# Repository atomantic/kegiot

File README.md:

Kegiot
=======
DIY Internet of Things (IoT) smart beverage dispenser.

This was a weekend hack project that turned into a maintained beverage dispenser.

I'll be giving a talk on this and touring the codebase as well as how the device was put together at [LinuxFest Northwest 2016](https://www.linuxfestnorthwest.org/2016)

Talk in progress: http://adameivy.com/presentation_kegerator/

# Warning
This codebase has been ported from a particular setup. Authentication was removed (as it was a proprietary setup).
The creator of this codebase assumes no responsibility for stolen beverages.

# Developer Getting Started
Assumes you are on OSX (yeah, we are opinionated).
You don't need to have a Beagle Bone Black connected to just run the app and test it. The app will mock all hardware interfaces.

```
# fork it
# clone it
cd kegiot
./dev init
```

This will make sure you have node.js and global module installations for `gulp`, `bower`, `npm-check` and will run `npm install && bower install`. Once ready, it will run `gulp`, which will launch the Admin UI. The UI will be running in `desktop` mode, which will mock all of the hardware interfaces (LCD, RFID scanner, temperature monitoring, ballvalve controller, etc).

## Authentication
This app has stripped out the authentication mechanism (because it was a proprietary auth service). You'll need to wire in your own to identify admin users or restrict access to the UI another way.
If you add auth:
* remove `.isAdmin.isAuthed` from `app/server/views/index.jade`
* re-enable the `requireAdmin` logic in `app/server/lib/common.js`
* remove default object keys from `app/client/js/app.js` in App.user (should be empty object)
* enable any place in the code where you find `authLib` (replace with auth solution)

## Slack notifications
You will need to supply your own slack hook URL as an env `SLACKHOOK` if you want the watchdog to notify temperature and keg volume limits as well as broadcast the location of the admin UI.

## Beagle Bone Black

0. Make sure you have setup a non-root user
```
apt-get update
useradd bbb
password bbb
password root
echo "bbb ALL=(ALL) ALL" >> /etc/sudoers
mkhomedir_helper bbb
mkdir -p /opt/kegiot
chown -R bbb:bbb /opt/kegiot
su bbb
chsh /bin/bash
curl -o- https://raw.githubusercontent.com/creationix/nvm/v0.31.1/install.sh | bash
. ~/.bashrc
nvm install 4.4.5
```
1. Plugin an ethernet cable and USB
2. Run the BBB install script
```
./dev install
```
3. Deploy the code
```
./dev deploy
```

## Deploy to the Bone branch
in order to allow the Beagleboard to not have to install gulp, sass, etc and build the project on the board, we publish the built output of the UI (post-sass) via:
```
gulp deploy
```
After that, we can `git pull` on the Beagleboard and we've got the built UI.
This assumes you went through and installed git, created an ssh key on the board (if needed) and deployed the whole codebase via git.
Alternatively, you can use the `dev` script to continue to deploy partial code without rebuilds or git.

## Guides
http://elinux.org/Beagleboard:BeagleBoneBlack_Debian

http://beagleboard.org/support/bonescript

## i2c (LCD)

Check the pinout here: http://beagleboard.org/static/images/cape-headers.png

Connect the Ground, 5v, 3v, clock, data to the bbb.
skip VDD_5V as it is only available when the Bone is plugged into the 5V power outlet. You can use the SYS_5V when only plugged into USB on your computer.

http://www.bibase.com/ascii.htm

```
ssh root@192.168.7.2
root@beaglebone:/var/lib/cloud9/myScripts# i2cset 1 0x04 0x63 0x40 0x00 0x00 i
root@beaglebone:/var/lib/cloud9/myScripts# i2cset 1 0x04 0x68 0x40 0x00 0x00 i
root@beaglebone:/var/lib/cloud9/myScripts# i2cset 1 0x04 0x70 0x00 0x00 0x00 0x48 0x69 0x64 0x65 0x79 0x20 0x68 0x6F i
```

The above are the commands that clear the lcd, home the cursor and print the message "Hidey ho"

# License
ISC

# Contributing
We welcome pull-requests. Feel free to fork, and deviate! Drink on.

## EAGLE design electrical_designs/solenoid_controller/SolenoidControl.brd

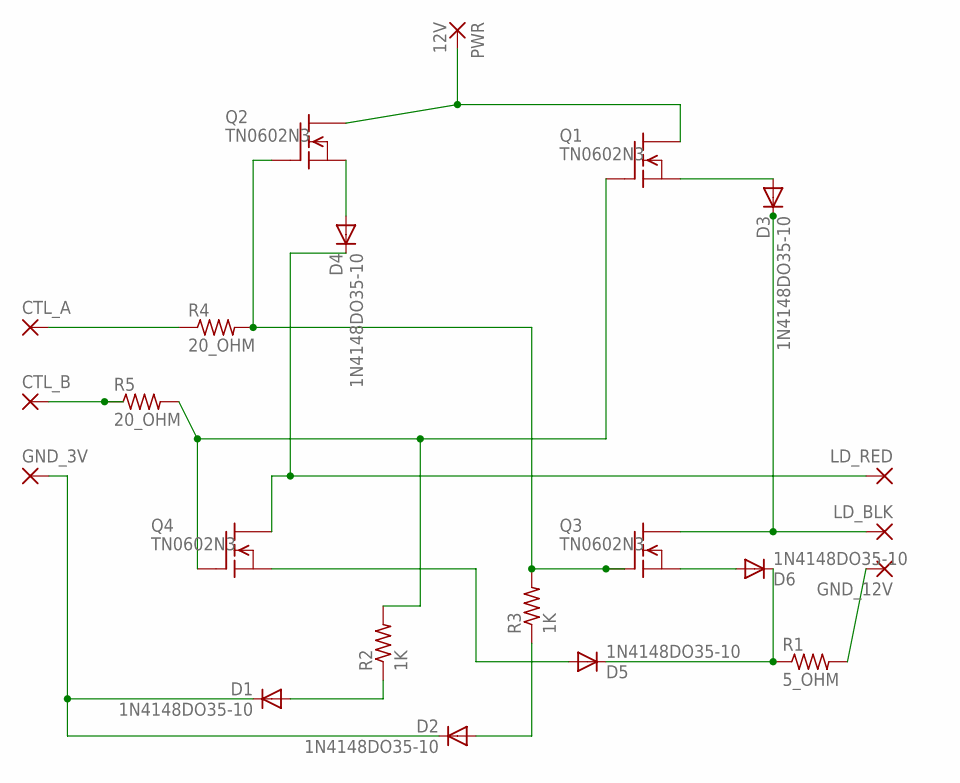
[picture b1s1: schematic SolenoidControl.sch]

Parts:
CTL_A: 2,15/1,0
CTL_B: 2,15/1,0
D1, D2, D3, D4, D5, D6: 1N4148DO35-10; DO35-10
GND_3V, GND_12V: 2,15/1,0
LD_BLK: 2,15/1,0
LD_RED: 2,15/1,0
PWR: 12V; 2,15/1,0
Q1, Q2, Q3, Q4: TN0602N3; TO-92
R1: 5_OHM; 0207/12
R2, R3: 1K; 0207/12
R4, R5: 20_OHM; 0207/12

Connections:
unnamed: PWR.1, Q1.3 (D), Q2.3 (D)
unnamed: D3.A, Q1.1 (S)
unnamed: D4.A, Q2.1 (S)
unnamed: D4.C, LD_RED.1, Q4.3 (D)
unnamed: D3.C, LD_BLK.1, Q3.3 (D)
unnamed: GND_12V.1, R1.2
unnamed: D5.A, Q4.1 (S)
unnamed: D2.A, R3.1
unnamed: Q2.2 (G), Q3.2 (G), R3.2, R4.2
unnamed: Q1.2 (G), Q4.2 (G), R2.2, R5.2
unnamed: CTL_B.1, R5.1
unnamed: CTL_A.1, R4.1
unnamed: D1.A, R2.1
unnamed: D1.C, D2.C, GND_3V.1
unnamed: D5.C, D6.C, R1.1
unnamed: D6.A, Q3.1 (S)

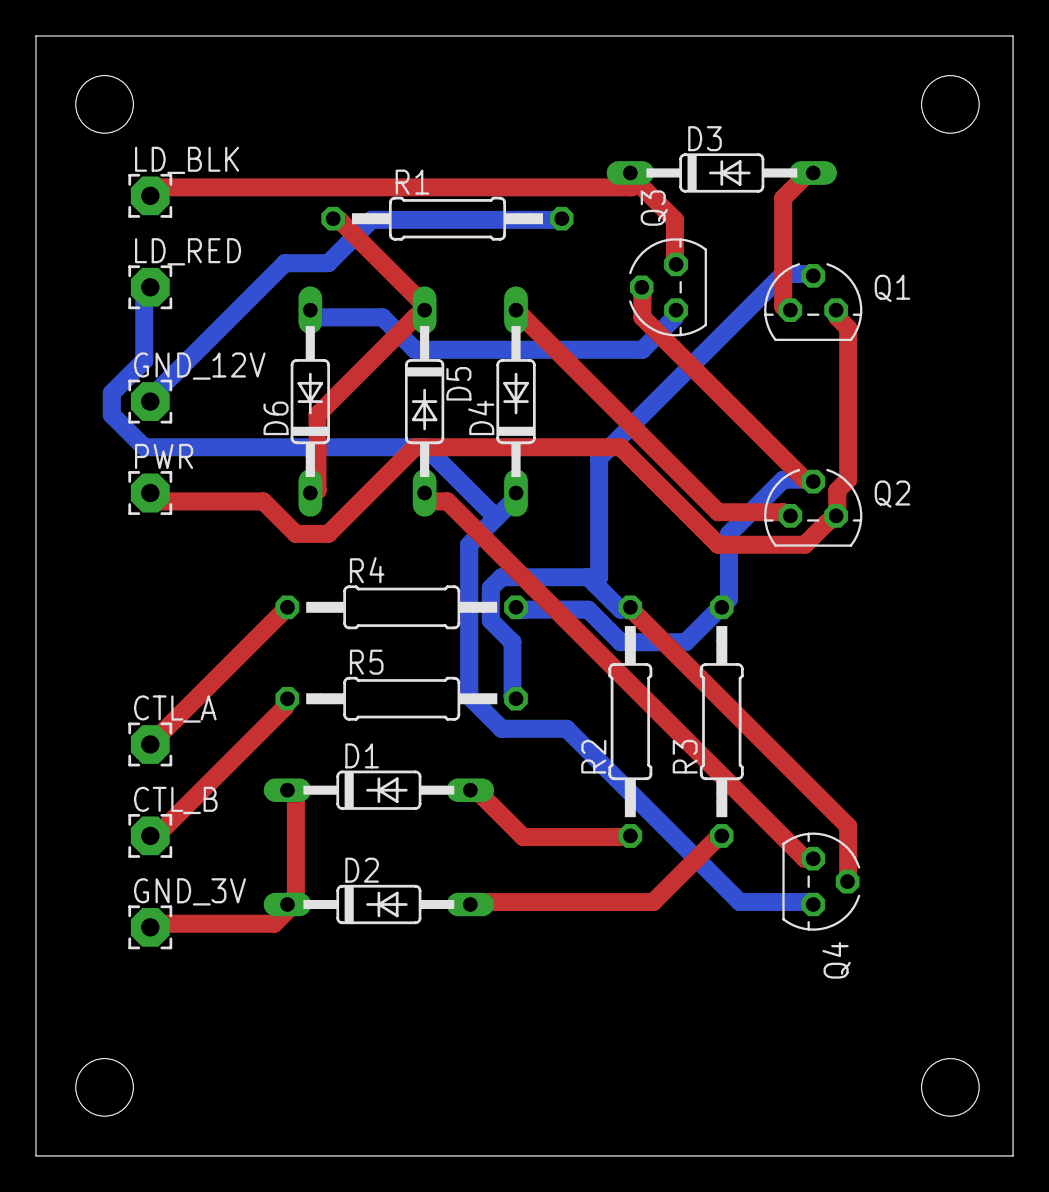
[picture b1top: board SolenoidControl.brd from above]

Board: 2 copper layers, 54.3 x 62.2 mm, 22 parts (0 on the bottom side), 16 nets.

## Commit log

2016-03-25 initial port of codebase
2016-03-25 move slack hook url to ENV so it does not end up in source control
2016-03-25 remove config value
2016-04-07 update deployment and bbb setup
2016-04-07 fix backgrid link
2016-04-07 clean up packages
2016-04-07 move server.error to lib file
2016-04-07 adding confirmation dialog when deleting things
2016-04-07 adding more steps and instruction to BBB install script
2016-04-07 ask if RFID reader is plugged in
2016-04-07 more modular
2016-04-22 fix app refactor
2016-04-22 modularize watchdogs
2016-04-22 eslint fixes
2016-04-22 gulp-eslint
2016-04-22 uniform config types
2016-04-22 remove extra dep on `debug`
2016-04-22 main is `server/app.js`
2016-04-22 modularize rfid.onUserScan
2016-05-03 fix bugs in rate_limit
2016-05-03 fix bug with uuid gen
2016-05-03 once more, with feeling
2016-05-03 remove some verbose network lib logging
2016-06-01 fix issue with rate limiting a new user
2016-06-02 setup non-root user
2016-06-02 keep it simple
2016-06-02 mkhomedir_helper bbb
